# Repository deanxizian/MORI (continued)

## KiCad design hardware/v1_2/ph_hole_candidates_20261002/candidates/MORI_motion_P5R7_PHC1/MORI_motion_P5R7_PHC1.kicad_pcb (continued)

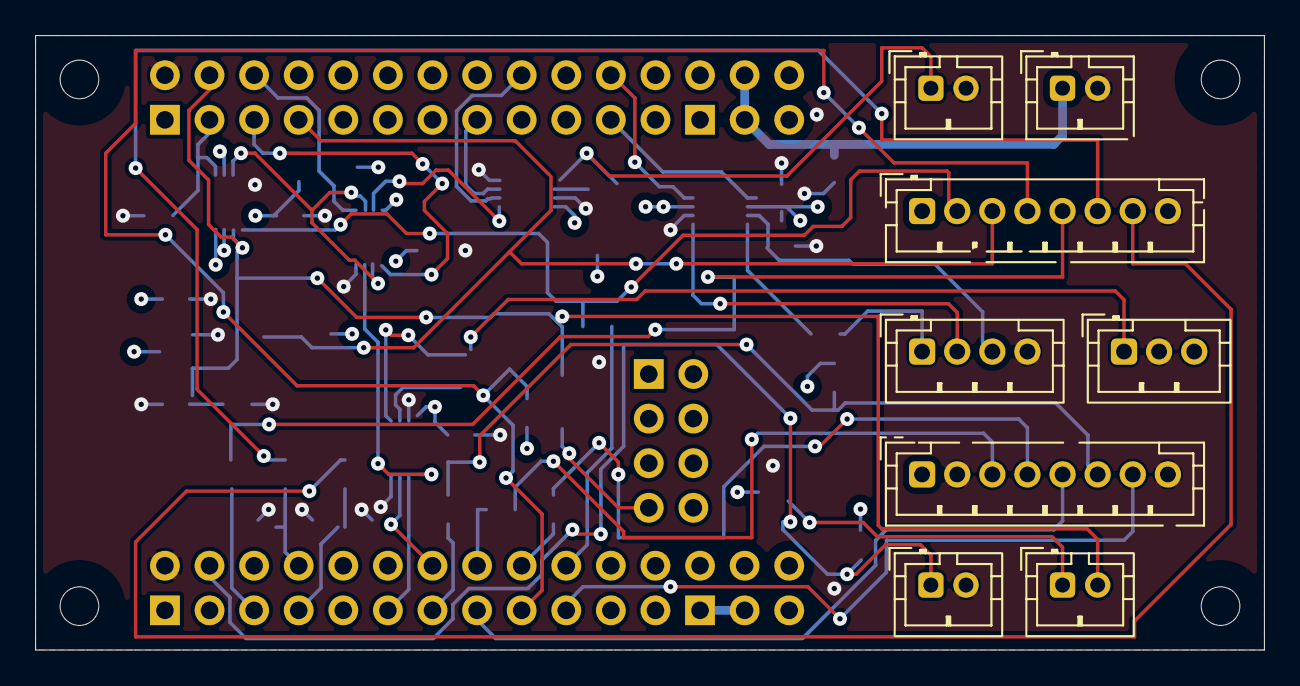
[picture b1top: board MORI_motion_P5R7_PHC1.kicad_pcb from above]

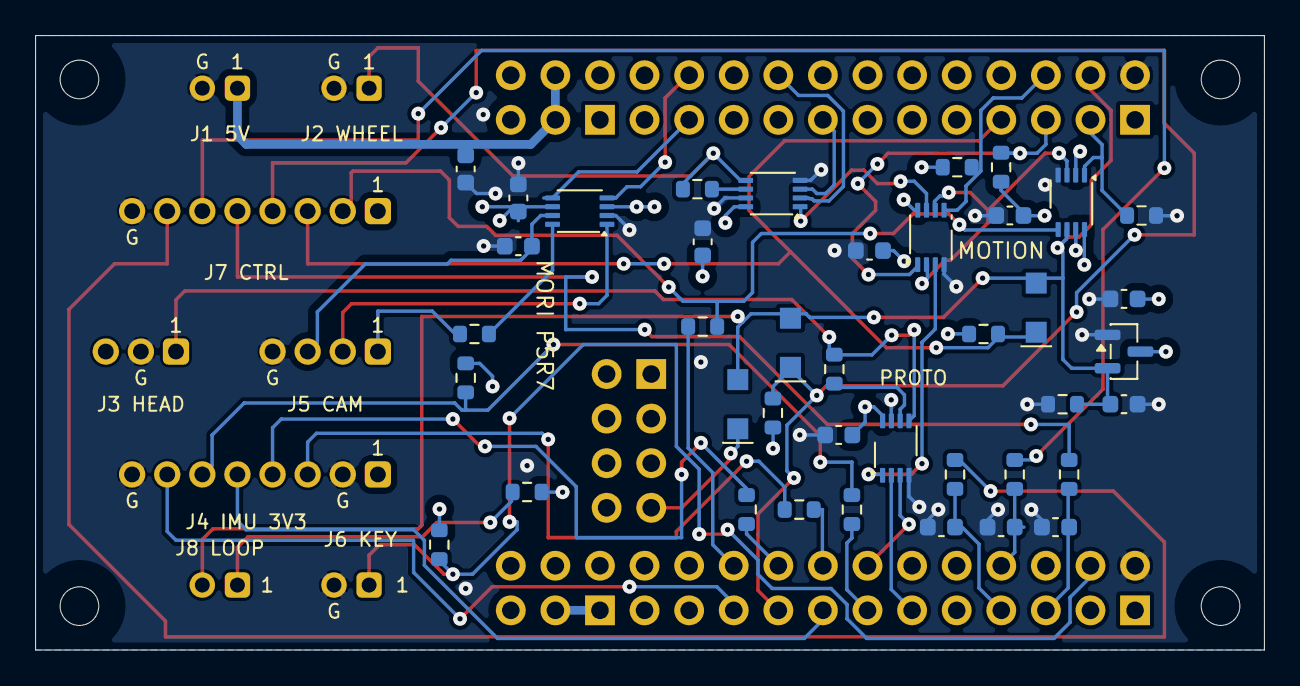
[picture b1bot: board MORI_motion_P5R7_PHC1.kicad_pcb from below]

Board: 4 copper layers, 70.0 x 35.0 mm, 53 parts (40 on the bottom side), 45 nets.

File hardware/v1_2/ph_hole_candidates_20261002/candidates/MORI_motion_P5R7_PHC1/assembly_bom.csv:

ref,value,footprint,source,note
U100,WeAct STM32F412RET6 64Pin V1.1,MORI_Custom:WeAct_F4_64Pin_V11_ECorrected_P5R7,https://github.com/WeActStudio/WeActStudio.STM32F4_64Pin_CoreBoard,"A=P1 B=P2 C=P3 D=P4 E=P5. Component side UP; all male pins DOWN from core underside. E pads shifted native X+2.54mm. Only E7 NRST is connected on carrier; other E pins NC on carrier. E8 is core3V3, not a carrier supply input. Candidate female sockets 61303021821x2 +61300821821; straight E male61300821121. Stack/mating/retention NOT_TESTED; see formal P5R7 handoff. Top SWD test access needs mechanical confirmation after changing from right-angle E header."
J1,MOTION 5V IN,MORI_Custom:JST_PH_B2B-PH-K_1x02_P2.00mm_Vertical__P4_PH_ANNULUS__P5_J1__PHC1_H85_L145,https://www.jst-mfg.com/product/pdf/eng/ePH.pdf,P4 PH 2.0 mm. PHR-2 / SPH-002T-P0.5S. Signal pin numbering unchanged. Check both mating views; never wire by color alone.
J2,S288 DATA ONLY,MORI_Custom:JST_PH_B2B-PH-K_1x02_P2.00mm_Vertical__P4_PH_ANNULUS__PHC1_H85_L145,https://www.jst-mfg.com/product/pdf/eng/ePH.pdf,P4 PH 2.0 mm. PHR-2 / SPH-002T-P0.5S. Signal pin numbering unchanged. Check both mating views; never wire by color alone.
J3,HEAD DATA ONLY,MORI_Custom:JST_PH_B3B-PH-K_1x03_P2.00mm_Vertical__P4_PH_ANNULUS__PHC1_H90_L150,https://www.jst-mfg.com/product/pdf/eng/ePH.pdf,P4 PH 2.0 mm. PHR-3 / SPH-002T-P0.5S. Signal pin numbering unchanged. Check both mating views; never wire by color alone.
J4,BODY IMU SPI,MORI_Custom:JST_PH_B8B-PH-K_1x08_P2.00mm_Vertical__P4_PH_ANNULUS__P5_J4__PHC1_H90_L150,https://www.jst-mfg.com/product/pdf/eng/ePH.pdf,P4 PH 2.0 mm. PHR-8 / SPH-002T-P0.5S. Signal pin numbering unchanged. Check both mating views; never wire by color alone.
J5,CAM J11 MATCH,MORI_Custom:JST_PH_B4B-PH-K_1x04_P2.00mm_Vertical__P4_PH_ANNULUS__PHC1_H90_L150,https://www.jst-mfg.com/product/pdf/eng/ePH.pdf,P4 PH 2.0 mm. PHR-4 / SPH-002T-P0.5S. Signal pin numbering unchanged. Check both mating views; never wire by color alone.
J6,INTERNAL SERVICE KEY,MORI_Custom:JST_PH_B2B-PH-K_1x02_P2.00mm_Vertical__P4_PH_ANNULUS__PHC1_H85_L145,https://www.jst-mfg.com/product/pdf/eng/ePH.pdf,P4 PH 2.0 mm. PHR-2 / SPH-002T-P0.5S. Signal pin numbering unchanged. Check both mating views; never wire by color alone.
J7,POWER CONTROL,MORI_Custom:JST_PH_B8B-PH-K_1x08_P2.00mm_Vertical__P4_PH_ANNULUS__P3R1_J7__PHC1_H90_L150,https://www.jst-mfg.com/product/pdf/eng/ePH.pdf,P4 PH 2.0 mm. PHR-8 / SPH-002T-P0.5S. Signal pin numbering unchanged. Check both mating views; never wire by color alone.
J8,LATCHED ENABLE LOOP,MORI_Custom:JST_PH_B2B-PH-K_1x02_P2.00mm_Vertical__P4_PH_ANNULUS__PHC1_H85_L145,https://www.jst-mfg.com/product/pdf/eng/ePH.pdf,P4 PH 2.0 mm. PHR-2 / SPH-002T-P0.5S. Signal pin numbering unchanged. Check both mating views; never wire by color alone.
U1,SN74LVC2G125DCUR,MORI_Custom:TI_DCU0008A_0p85x0p30,https://www.ti.com/lit/ds/symlink/sn74lvc2g125.pdf,Ioff; bus input 0..5.5V. External actuator VIH/VOH not yet verified. Default no transmission.
U2,SN74LVC2G125DCUR,MORI_Custom:TI_DCU0008A_0p85x0p30__P5_U2,https://www.ti.com/lit/ds/symlink/sn74lvc2g125.pdf,Ioff; bus input 0..5.5V. External actuator VIH/VOH not yet verified. Default no transmission.
U3,SN74LVC2G32DCUR,MORI_Custom:TI_DCU0008A_0p85x0p30__P5_U3,https://www.ti.com/lit/ds/symlink/sn74lvc2g32.pdf,
U4,TXU0202DCUR,MORI_Custom:TI_DCU0008A_0p85x0p30,https://www.ti.com/lit/ds/symlink/txu0202.pdf,"VCC isolation and Ioff; J11.3 powers only translator B rail, never feeds motion regulator."
U5,SN74LVC1G74DCUR,MORI_Custom:TI_DCU0008A_0p85x0p30__P5_U5,https://www.ti.com/lit/ds/symlink/sn74lvc1g74.pdf,Physical loop + supervisor + faults clear latch; only a new explicit ARM rising edge re-enables.
U6,TLV803EA29DBZR,Package_TO_SOT_SMD:SOT-23,https://www.ti.com/lit/ds/symlink/tlv803e.pdf,"2.93V threshold,200ms reset; exact non-R/non-V pinout."
D1,"BAT54H,115",MORI_Custom:BAT54H_SOD123F_Nexperia_20241008_P5R6,,"Cathode pin1; pulls latch clear low, does not reset MCU on ordinary disable."
D2,"BAT54H,115",MORI_Custom:BAT54H_SOD123F_Nexperia_20241008_P5R6,,"Cathode pin1; pulls latch clear low, does not reset MCU on ordinary disable."
D3,"BAT54H,115",MORI_Custom:BAT54H_SOD123F_Nexperia_20241008_P5R6,,"Cathode pin1; pulls latch clear low, does not reset MCU on ordinary disable."
R1,68,Resistor_SMD:R_0603_1608Metric,,
R2,68,Resistor_SMD:R_0603_1608Metric,,
R3,10k,Resistor_SMD:R_0603_1608Metric,,
R4,10k,Resistor_SMD:R_0603_1608Metric,,
R5,10k,Resistor_SMD:R_0603_1608Metric,,
R6,1k,Resistor_SMD:R_0603_1608Metric,,
R7,10k,Resistor_SMD:R_0603_1608Metric,,
R8,10k,Resistor_SMD:R_0603_1608Metric,,
R9,47,Resistor_SMD:R_0603_1608Metric,,
R10,33,Resistor_SMD:R_0603_1608Metric,,
R11,33,MORI_Custom:R_0603_1608Metric__P5_R11,,
R12,33,Resistor_SMD:R_0603_1608Metric,,
R13,10k,Resistor_SMD:R_0603_1608Metric,,
R14,1k,Resistor_SMD:R_0603_1608Metric,,
R15,1k,Resistor_SMD:R_0603_1608Metric,,
R16,1k,Resistor_SMD:R_0603_1608Metric,,
R17,10k,Resistor_SMD:R_0603_1608Metric,,
R18,10k,Resistor_SMD:R_0603_1608Metric,,
R19,1k,Resistor_SMD:R_0603_1608Metric,,
C1,100n,Capacitor_SMD:C_0603_1608Metric,,
C2,100n,Capacitor_SMD:C_0603_1608Metric,,
C3,100n,MORI_Custom:C_0603_1608Metric__P5_C3,,
C4,100n,Capacitor_SMD:C_0603_1608Metric,,
C5,100n,Capacitor_SMD:C_0603_1608Metric,,
C6,100n,Capacitor_SMD:C_0603_1608Metric,,
C7,100n,Capacitor_SMD:C_0603_1608Metric,,
C8,10u,Capacitor_SMD:C_0603_1608Metric,,
C9,10n,Capacitor_SMD:C_0603_1608Metric,,
C10,10n,MORI_Custom:C_0603_1608Metric__P5_C10,,
C11,10n,MORI_Custom:C_0603_1608Metric__P5_C11,,
C12,100n,Capacitor_SMD:C_0603_1608Metric,,
H1,M2 clearance,MountingHole:MountingHole_2.2mm_M2,,
H2,M2 clearance,MountingHole:MountingHole_2.2mm_M2,,
H3,M2 clearance,MountingHole:MountingHole_2.2mm_M2,,
H4,M2 clearance,MountingHole:MountingHole_2.2mm_M2,,

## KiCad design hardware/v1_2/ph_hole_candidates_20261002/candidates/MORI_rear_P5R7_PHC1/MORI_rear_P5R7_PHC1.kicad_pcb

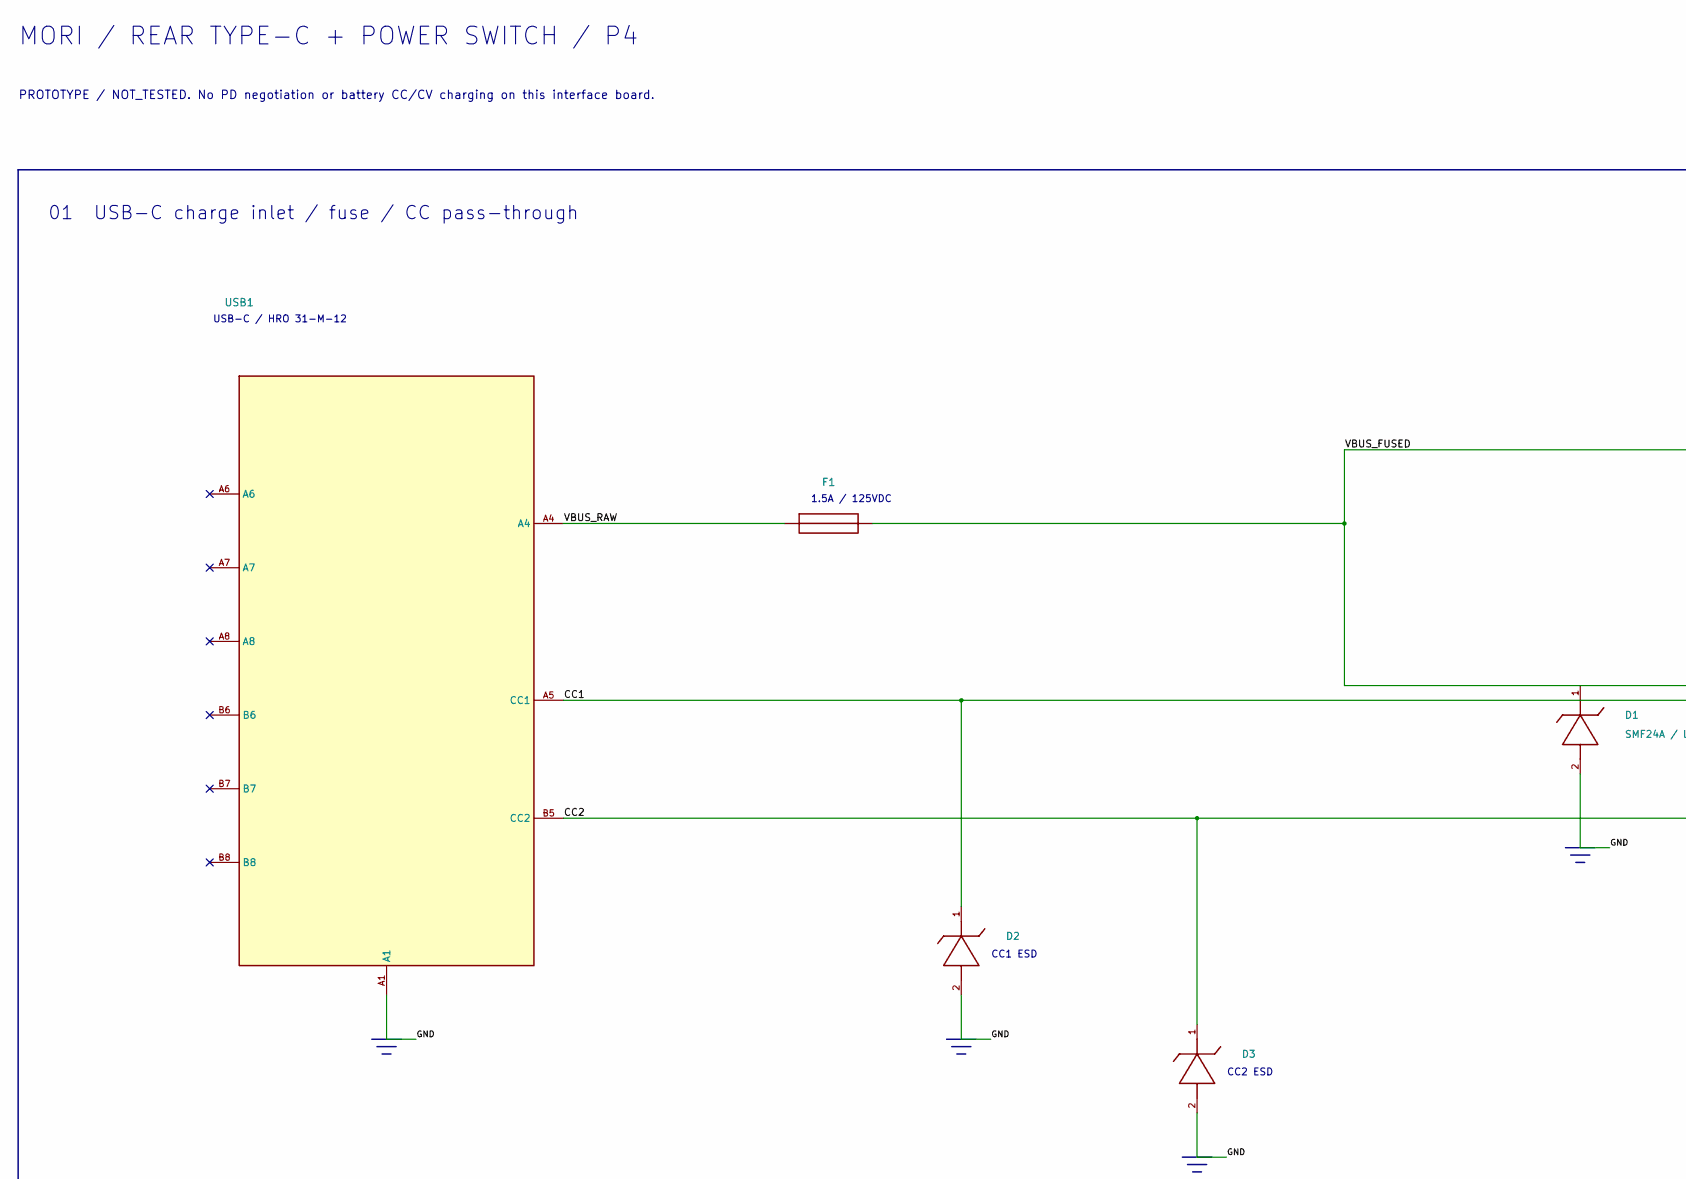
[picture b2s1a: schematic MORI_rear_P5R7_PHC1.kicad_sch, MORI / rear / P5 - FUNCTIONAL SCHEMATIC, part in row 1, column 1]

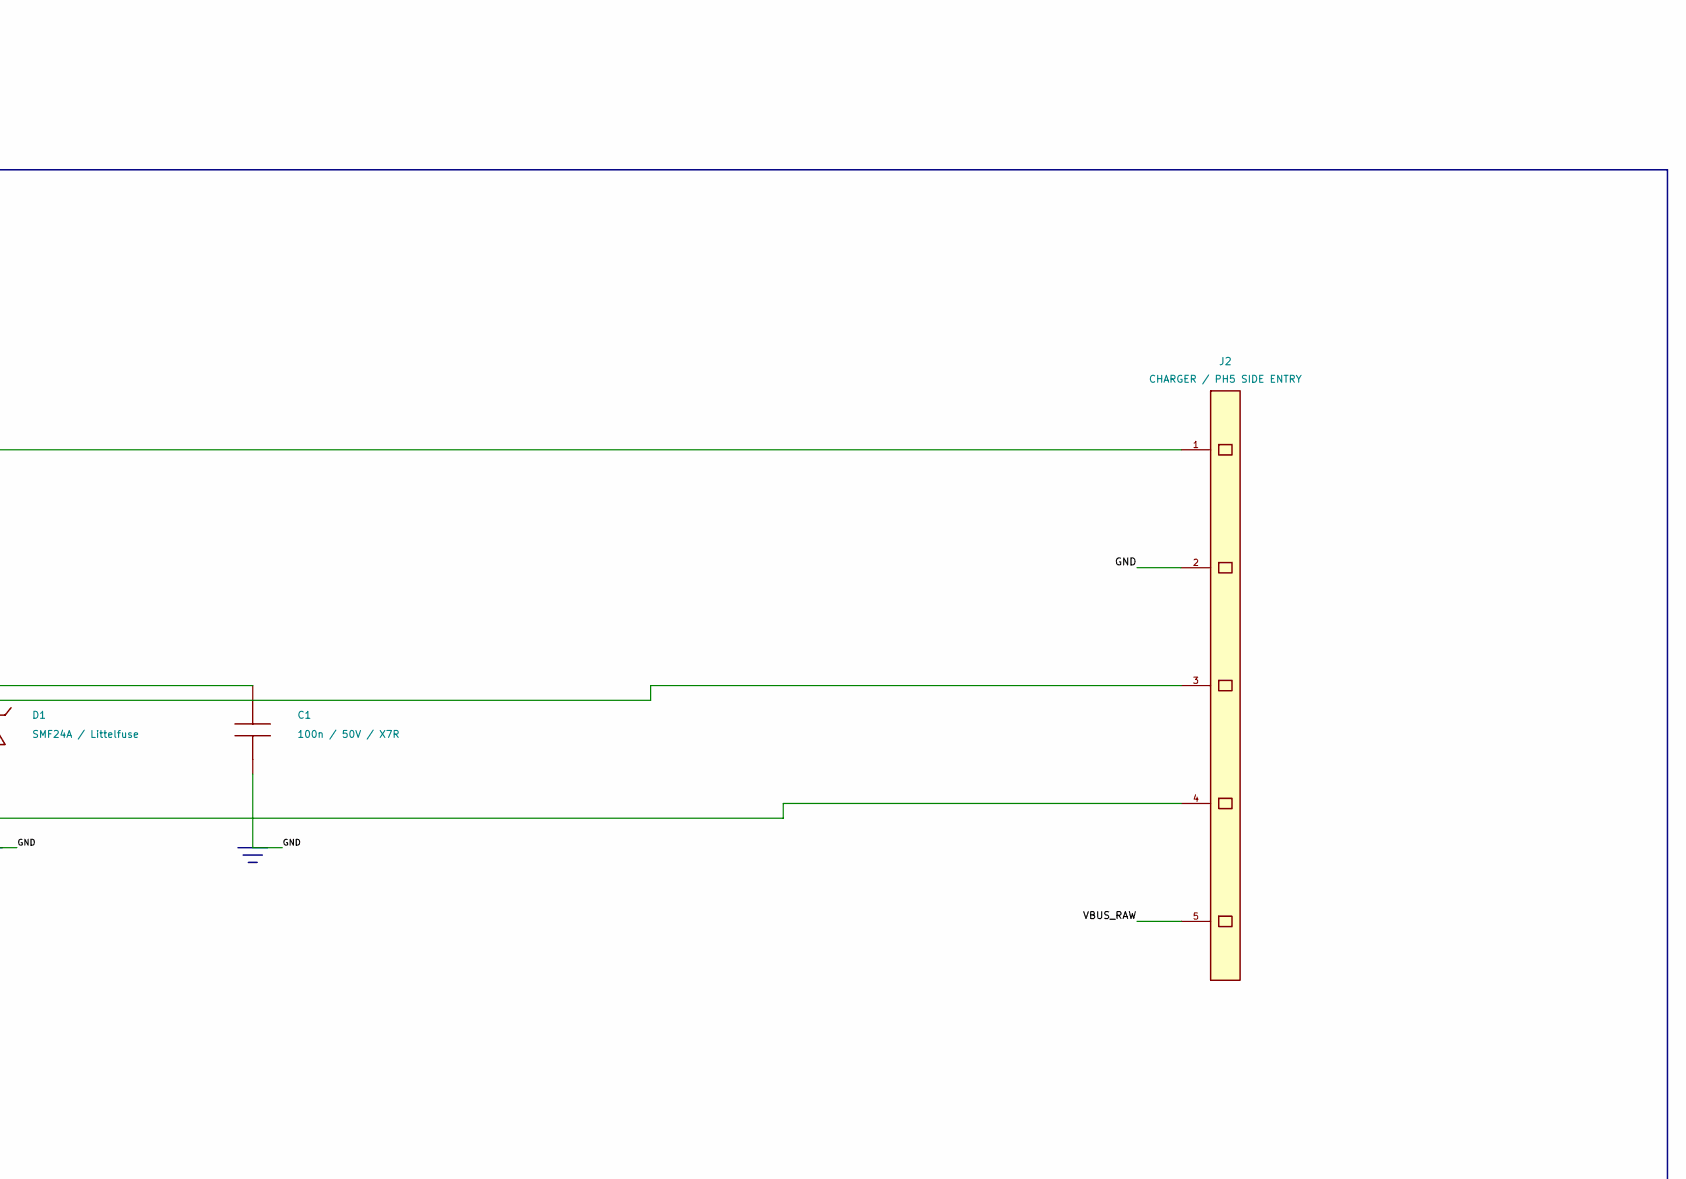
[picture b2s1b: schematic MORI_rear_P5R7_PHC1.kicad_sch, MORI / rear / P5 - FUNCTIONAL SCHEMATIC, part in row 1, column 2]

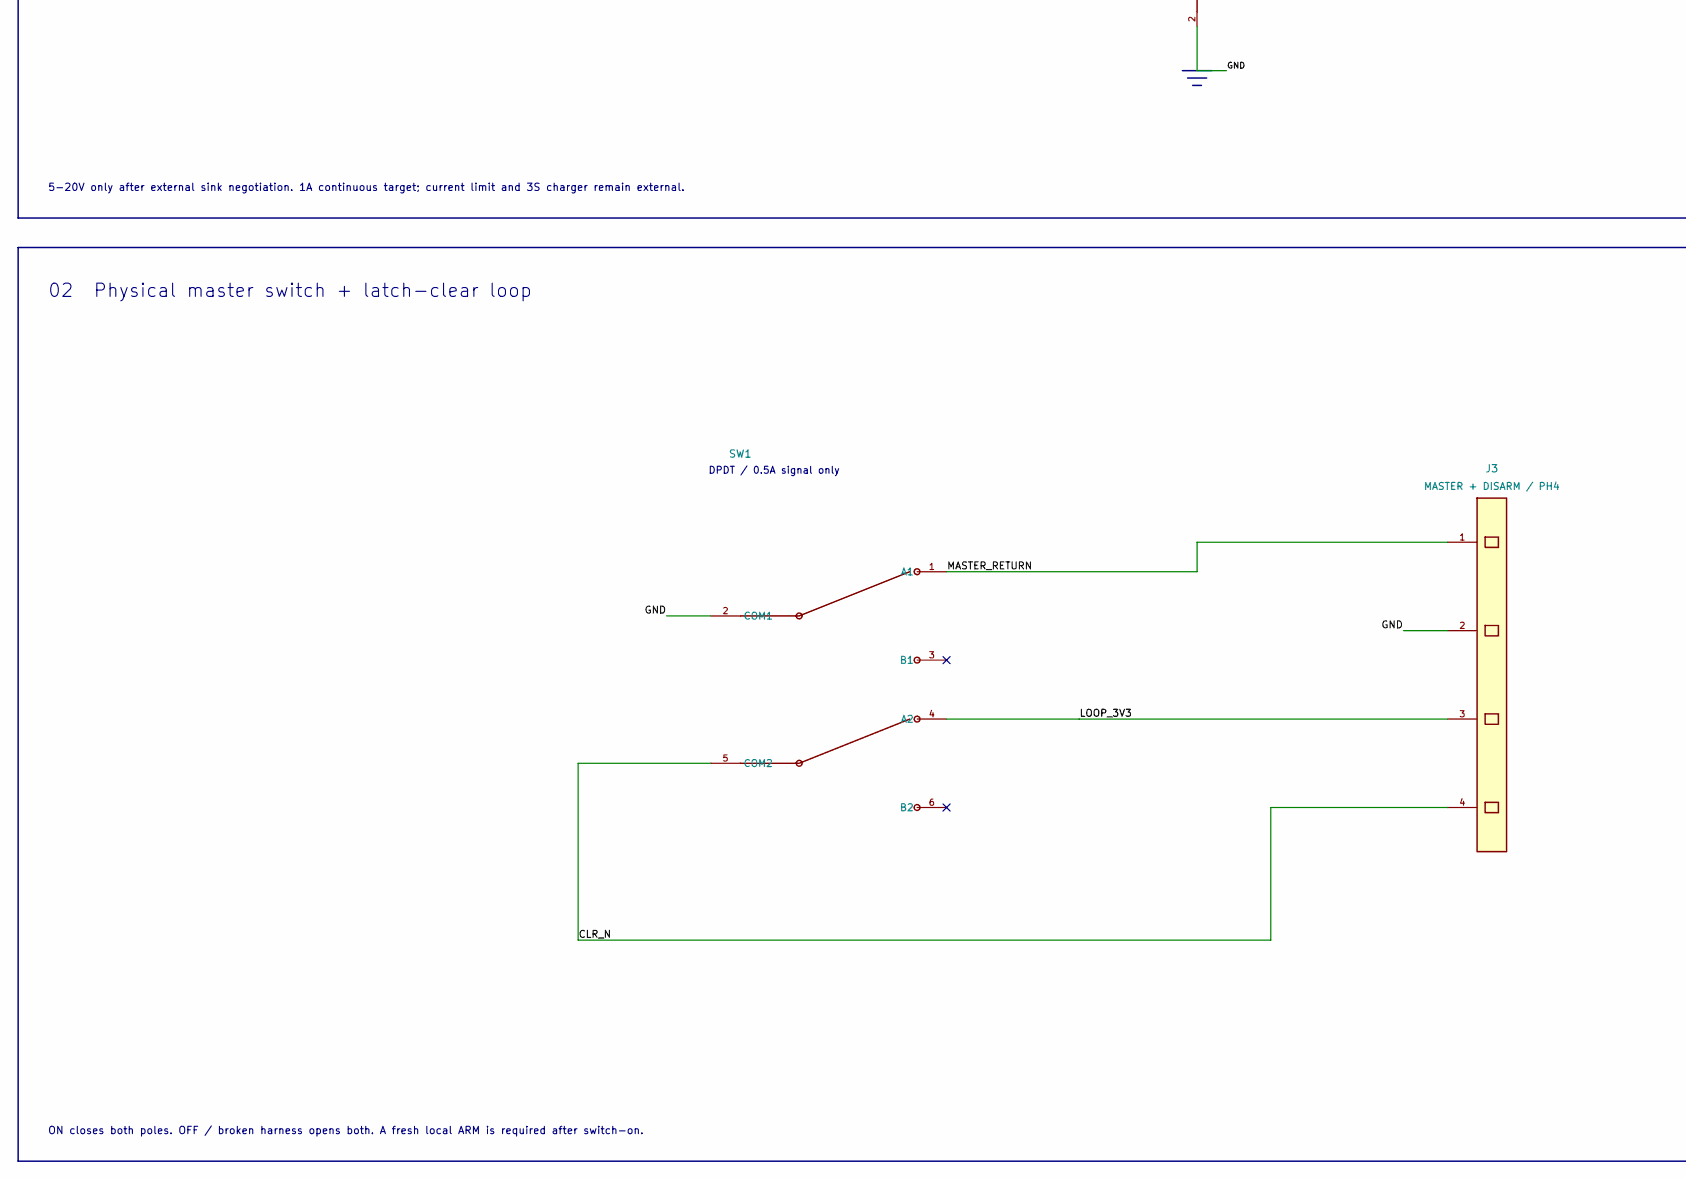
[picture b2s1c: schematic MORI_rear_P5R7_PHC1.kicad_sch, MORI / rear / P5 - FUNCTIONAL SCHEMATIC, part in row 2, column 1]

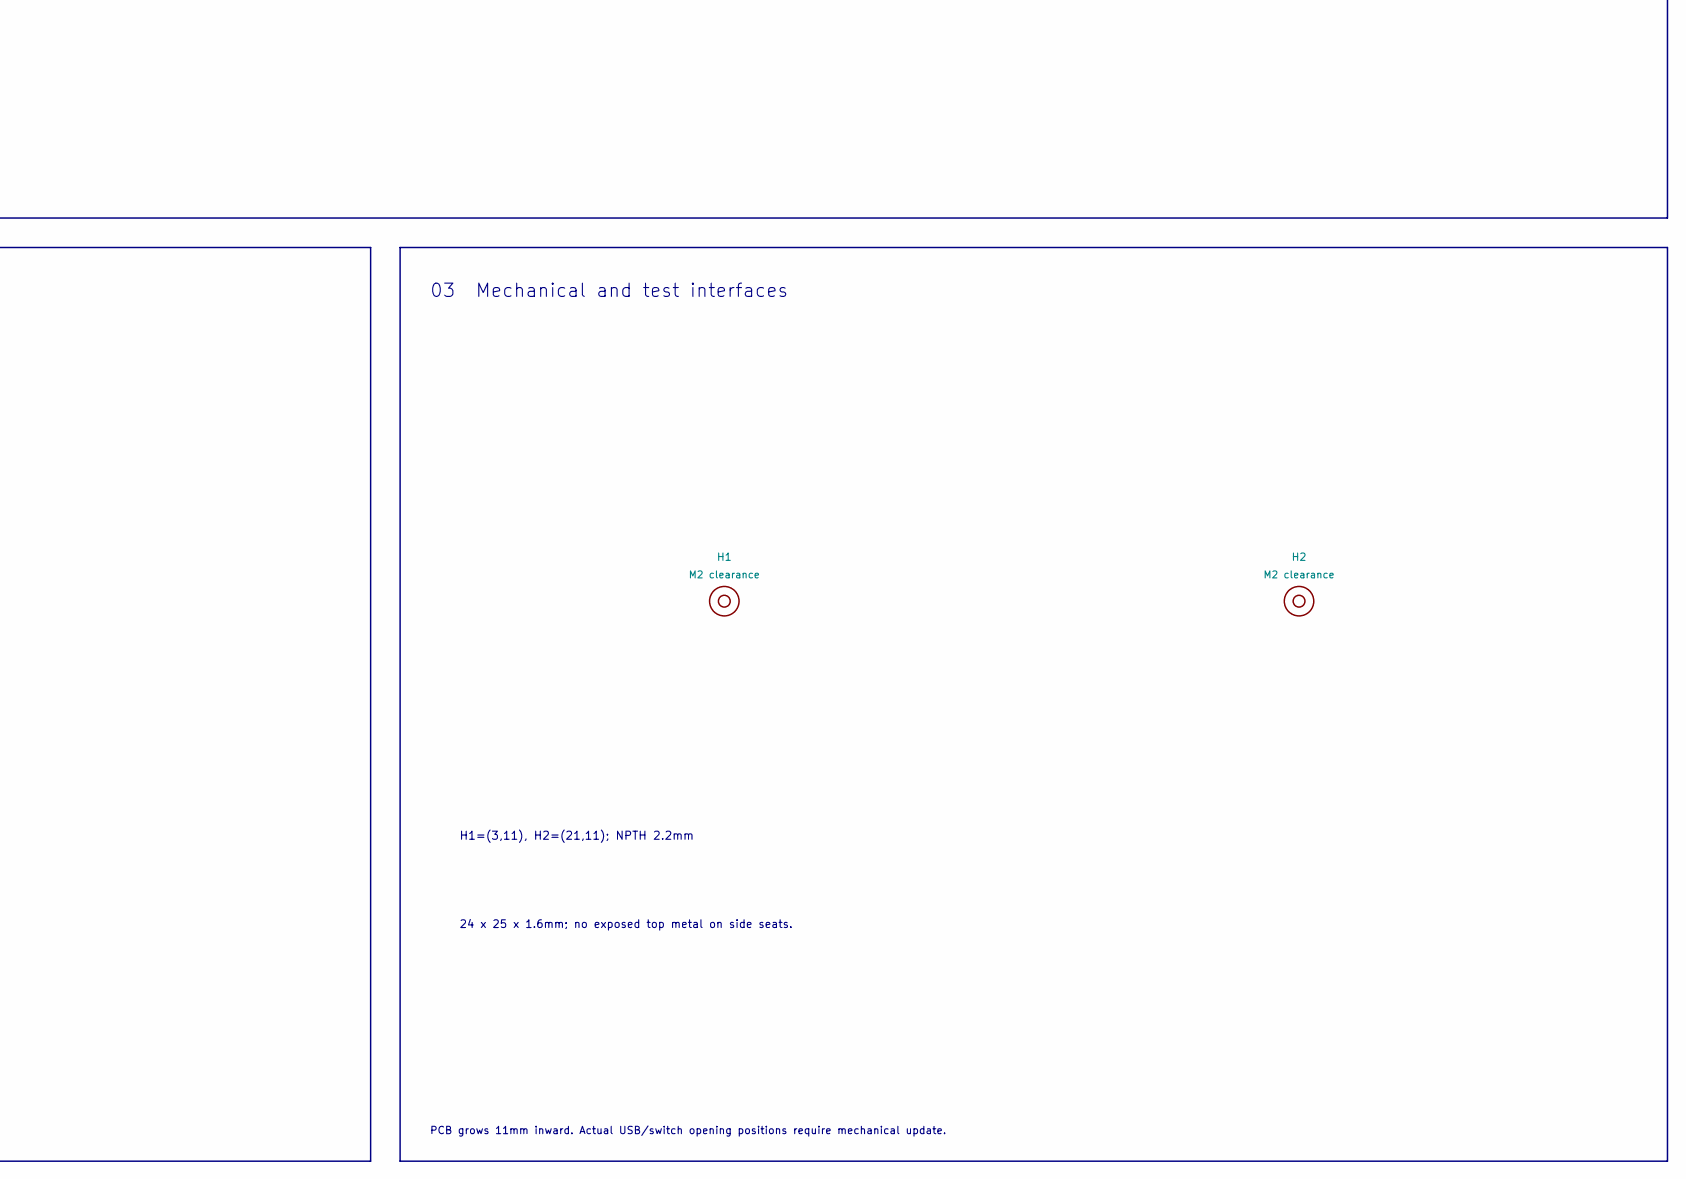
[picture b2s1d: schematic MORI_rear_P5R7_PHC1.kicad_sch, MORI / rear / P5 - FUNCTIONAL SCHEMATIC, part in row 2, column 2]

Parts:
C1: 100n / 50V / X7R; C_0603_1608Metric
D1: SMF24A / Littelfuse; D_SOD-123F__P5_D1
D2: PESD5V0L1BA,115; D_SOD-323__P5_D2
D3: PESD5V0L1BA,115; D_SOD-323__P5_D3
F1: 045101.5MRL / 1.5A; Littelfuse_451_6.1x2.69_P4__P3R1_F1
H1, H2: M2 clearance; MountingHole_2.2mm_M2
J2: CHARGER / PH5 SIDE ENTRY; JST_PH_S5B-PH-K_1x05_P2.00mm_Horizontal__P4_ANNULUS__P5_J2_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
J3: MASTER + DISARM / PH4; JST_PH_B4B-PH-K_1x04_P2.00mm_Vertical__P4_ANNULUS__P3R1_J3_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
SW1: SOFNG MS-202V-G3; SOFNG_MS202V_G3_P4__P5_SW1
USB1: HRO TYPE-C-31-M-12 / charge only; USB_C_Receptacle_HRO_TYPE-C-31-M-12__P4_ANNULUS__P5_USB1

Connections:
/CC1: D2.1, J2.3, USB1.A5 (CC1)
/CC2: D3.1, J2.4, USB1.B5 (CC2)
/CLR_N: J3.4, SW1.5 (COM2)
/GND: C1.2, D1.2, D2.2, D3.2, J2.2, J3.2, SW1.2 (COM1), USB1.A1, USB1.A12, USB1.B1, USB1.B12, USB1.SH
/LOOP_3V3: J3.3, SW1.4 (A2)
/MASTER_RETURN: J3.1, SW1.1 (A1)
/VBUS_FUSED: C1.1, D1.1, F1.2, J2.1
/VBUS_RAW: F1.1, J2.5, USB1.A4, USB1.A9, USB1.B4, USB1.B9

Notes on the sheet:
MORI / REAR TYPE-C + POWER SWITCH / P4
PROTOTYPE / NOT_TESTED. No PD negotiation or battery CC/CV charging on this interface board.
01 USB-C charge inlet / fuse / CC pass-through
5-20V only after external sink negotiation. 1A continuous target; current limit and 3S charger remain external.
USB-C / HRO 31-M-12
1.5A / 125VDC
CC1 ESD
CC2 ESD
02 Physical master switch + latch-clear loop
ON closes both poles. OFF / broken harness opens both. A fresh local ARM is required after switch-on.
DPDT / 0.5A signal only
03 Mechanical and test interfaces
PCB grows 11mm inward. Actual USB/switch opening positions require mechanical update.
H1=(3,11), H2=(21,11); NPTH 2.2mm
24 x 25 x 1.6mm; no exposed top metal on side seats.

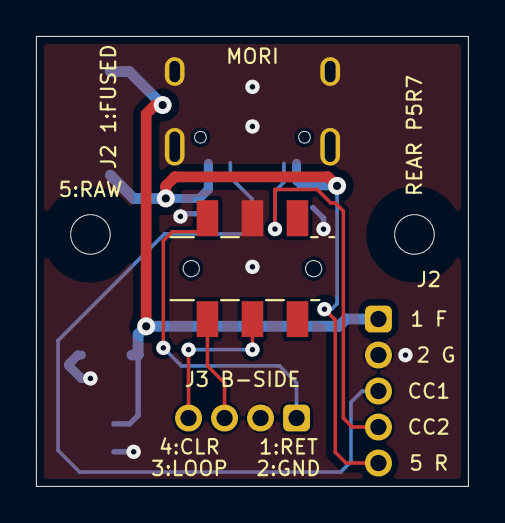
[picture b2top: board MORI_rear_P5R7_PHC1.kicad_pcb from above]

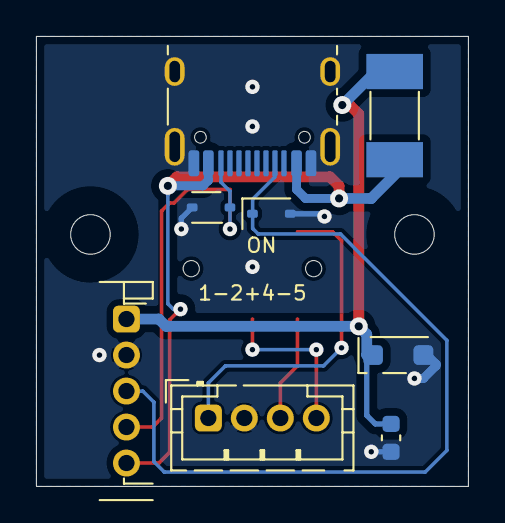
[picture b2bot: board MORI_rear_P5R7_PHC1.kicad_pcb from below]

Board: 2 copper layers, 24.0 x 25.0 mm, 11 parts (8 on the bottom side), 8 nets.

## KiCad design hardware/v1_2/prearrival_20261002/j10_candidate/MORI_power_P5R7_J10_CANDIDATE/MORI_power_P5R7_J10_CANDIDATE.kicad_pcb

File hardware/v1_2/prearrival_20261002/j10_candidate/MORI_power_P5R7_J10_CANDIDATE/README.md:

# J10 侧出线试装候选 C1

PROTOTYPE / NOT FOR FABRICATION. 保持 P5R6 孔位、针序和铜线，仅变更 J10 封装及其本体规则区。原版不变。

此目录用于暴露固定孔位替换的碰撞，不能因有原生文件就称为通过。真实 DRC/ERC 与几何结果在 ../reports/。未导出生产文件，完整机械插拔与线束仍待复核。

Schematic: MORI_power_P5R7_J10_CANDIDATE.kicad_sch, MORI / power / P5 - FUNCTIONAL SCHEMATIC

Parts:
C1, C20: 100n; C_0603_1608Metric
C2: 1u 25V; C_0603_1608Metric__P3_C2
C10: Panasonic EEU-FR1C102 1000uF 16V; CP_Radial_D10.0mm_P5.00mm__P2_C10__P3_C10__P5_C10
C21, C41: 10n; C_0603_1608Metric
C30: Panasonic EEU-FR1C102 1000uF 16V; CP_Radial_D10.0mm_P5.00mm__P3_C30__P5_C30
C40: 100n; C_0603_1608Metric__P5_C40
C60: 22u / 25V / X7R; C_1210_3225Metric__P3_C60__P3R1_C60
C61: 100n / 50V / X7R; C_0603_1608Metric__P5_C61
C62, C72: 100n / 50V / X7R; C_0603_1608Metric
C63: 22u / 25V / X7R; C_1210_3225Metric__P5_C63
C64, C66, C73, C76: 22u / 25V / X7R; C_1210_3225Metric
C65: 75p / 50V / C0G; C_0603_1608Metric__P5_C65
C70: 22u / 25V / X7R; C_1210_3225Metric__P3_C70
C71: 100n / 50V / X7R; C_0603_1608Metric__P5_C71
C74: 22u / 25V / X7R; C_1210_3225Metric__P3_C74
C75: 75p / 50V / C0G; C_0603_1608Metric__P3R1_C75
D1, D20, D90: BZT52H-C10,115; D_SOD-123F
D10: B540C-13-F; D_SMC__P3_D10__P5_D10
D30: B540C-13-F; D_SMC__P5_D30
D40: BZT52H-C10,115; D_SOD-123F__P5_D40
F60: 1A / 125V / very fast; Fuse_Littelfuse-NANO2-451_453
F70: 2A / 125V / very fast; Fuse_Littelfuse-NANO2-451_453__P5_F70
H1, H2, H3, H4: M2 mounting / POSITION TBD; MountingHole_2.2mm_M2
J1: PACK AFTER 6.3A FUSE; AMASS_XT30UPB-M_1x02_P5.0mm_Vertical__P3_J1
J2: WHEEL BUCK VIN; AMASS_XT30UPB-M_1x02_P5.0mm_Vertical__P3_J2__P5_J2
J3: WHEEL BUCK 9V RETURN; AMASS_XT30UPB-M_1x02_P5.0mm_Vertical__P3R1_J3
J4: HEAD BUCK VIN; AMASS_XT30UPB-M_1x02_P5.0mm_Vertical__P2_J4__P3_J4__P3R1_J4
J5: HEAD BUCK 6V RETURN; AMASS_XT30UPB-M_1x02_P5.0mm_Vertical__P2_J5__P3_J5__P5_J5
J6: BAT_MON SERVICE / DNP; AMASS_XT30UPB-M_1x02_P5.0mm_Vertical__P3_J6__P3R1_J6; not fitted
J7: S288 L; JST_XH_B3B-XH-A_1x03_P2.50mm_Vertical__P2_J7__P3_J7__P5_J7
J8: S288 R; JST_XH_B3B-XH-A_1x03_P2.50mm_Vertical__P2_J8__P5_J8
J9: SCS0009 CHAIN; JST_XH_B3B-XH-A_1x03_P2.50mm_Vertical__P5_J9
J10: MOTION CONTROL; JST_PH_S8B-PH-K_1x08_P2.00mm_Horizontal__MORI_1p35land_0p75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
J11: WHEEL DUMP 5R6 EXTERNAL; AMASS_XT30UPB-M_1x02_P5.0mm_Vertical__P5R5_DUMP
J12: HEAD DUMP 10R EXTERNAL; AMASS_XT30UPB-M_1x02_P5.0mm_Vertical__P2_J12__P5_J12__P5R5_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
J13: S288 DATA; JST_PH_B2B-PH-K_1x02_P2.00mm_Vertical__P4_PH_ANNULUS
J14: HEAD DATA; JST_PH_B3B-PH-K_1x03_P2.00mm_Vertical__P4_PH_ANNULUS
J15: CHARGE INTERLOCK; JST_PH_B2B-PH-K_1x02_P2.00mm_Vertical__P4_PH_ANNULUS__P3R1_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
J16: CHARGER RAW VBUS SENSE; JST_PH_B2B-PH-K_1x02_P2.00mm_Vertical__P4_PH_ANNULUS__P3R1_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
J17: MOTION 5V OUT / 1+ 2GND; JST_PH_B2B-PH-K_1x02_P2.00mm_Vertical__P4_PH_ANNULUS
J18: CAM 5V OUT / 1+ 2GND; JST_XH_B2B-XH-A_1x02_P2.50mm_Vertical
J19: REAR MASTER / 1RETURN 2GND; JST_PH_B2B-PH-K_1x02_P2.00mm_Vertical__P4_PH_ANNULUS__P5_J19
JP60: SERVICE OFF / OPEN=ON; PinHeader_1x02_P2.54mm_Vertical__P3_JP60__P3R1_JP60
JP70: SERVICE OFF / OPEN=ON; PinHeader_1x02_P2.54mm_Vertical__P5_JP70
L60, L70: 10uH / SRP7050TA-100M; Bourns_SRP7050TA_8p4_span_2p5_gap
Q1: AO4407A; SOIC-8_3.9x4.9mm_P1.27mm__P5_Q1
Q10, Q90: AO4407A; SOIC-8_3.9x4.9mm_P1.27mm
Q11: AO3400A; SOT-23__P5_Q11
Q20, Q31, Q40: AO3400A; SOT-23
Q30: AO4407A; SOIC-8_3.9x4.9mm_P1.27mm__P5_Q30
Q50: MMBT3904LT1G; SOT-23__P5_Q50
R1, R30, R91: 10k; R_0603_1608Metric
R2: WSL2512R0100FEA 10mR 1% 1W; R_2512_6332Metric
R3, R4: 0; R_0603_1608Metric
R10: 10k; R_0603_1608Metric__P5_R10
R11: 100; R_0603_1608Metric__P5_R11
R20, R24, R40, R44: 2.2k; R_0603_1608Metric
R21: 33.2k 0.1%; R_0603_1608Metric
R22: 10k 0.1%; R_0603_1608Metric__P5_R22
R23, R43: 1M 0.1%; R_0603_1608Metric
R25: 37.4k 0.1%; R_0603_1608Metric
R26, R42, R46: 10k 0.1%; R_0603_1608Metric
R31: 100; R_0603_1608Metric__P5_R31
R41: 16.5k 0.1%; R_0603_1608Metric
R45: 18.7k 0.1%; R_0603_1608Metric__P5_R45
R50, R52: 100k 0.1%; R_0603_1608Metric
R51, R53: 27k 0.1%; R_0603_1608Metric
R54: 10k; R_0603_1608Metric__P5_R54
R55: 47k; R_0603_1608Metric
R56: 100k; R_0603_1608Metric__P5_R56
R60, R70: 100k / 0.1%; R_0603_1608Metric
R61: 13.3k / 0.1%; R_0603_1608Metric
R71: 13.3k / 0.1%; R_0603_1608Metric__P3_R71
R90: 100k; R_0603_1608Metric
TP60: +5V_MOTION; TestPoint_Pad_D1.5mm__P3_TP60
TP61: GND; TestPoint_Pad_D1.5mm__P5_TP61
TP70: +5V_CAM; TestPoint_Pad_D1.5mm__P3R1_TP70
TP71: GND; TestPoint_Pad_D1.5mm__P5_TP71
U1: INA180A1IDBVR; SOT-23-5__P5_U1
U20: LM393BDR; SOIC-8_3.9x4.9mm_P1.27mm__P5_U20
U21: TL431BIDBZR; SOT-23
U40: LM393BDR; SOIC-8_3.9x4.9mm_P1.27mm__P5_U40
U41: TL431BIDBZR; SOT-23__P5_U41
U60, U70: TPS54302DDCR; TI_DDC0006A_TPS54302

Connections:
/+3V3: C1.1, J10.1, U1.5 (VS)
/+5V_CAM: C73.1, C74.1, C75.1, J18.1 (5V_OUT), L70.2, R70.1, TP70.1
/+5V_MOTION: C63.1, C64.1, C65.1, J17.1 (5V_OUT), L60.2, R60.1, TP60.1
/ARM_Q: J10.2, Q11.1, Q31.1, R54.1
/BAT_ADC: J10.5, R50.2, R51.1
/BAT_IN: Q1.5, Q1.6, Q1.7, Q1.8, Q90.5, Q90.6, Q90.7, Q90.8
/BAT_MON: C2.1, F60.1, F70.1, J2.2 (PLUS), J4.2 (PLUS), J6.2 (PLUS), R2.2, R4.1, R50.1
/BAT_REV: D1.1, Q1.1 (SOURCE PROTECTED OUTPUT), Q1.2, Q1.3, R2.1, R3.1
/C5_BOOT: C72.1, U70.6 (BOOT)
/C5_EN: JP70.1 (EN), U70.5 (EN)
/C5_FB: C75.2, R70.2, R71.1, U70.4 (FB)
/C5_SW: C72.2, L70.1, U70.2 (SW)
/C5_VIN: C70.1, C71.1, C76.1, F70.2, U70.3 (VIN)
/CHG_BASE: Q50.1 (B), R55.2, R56.1
/CHG_N: J10.4, J15.1, Q50.3 (C)
/CURRENT_ADC: J10.7, U1.1 (OUT)
/FAULT_N: J10.3, U20.7 (OUT2), U40.7 (OUT2)
/GND: C1.2, C2.2, C10.2, C20.2, C21.2, C30.2, C40.2, C41.2, C60.2, C61.2, C63.2, C64.2, C66.2, C70.2, C71.2, C73.2, C74.2, C76.2, D20.2, D40.2, J1.1 (MINUS), J2.1 (MINUS), J3.1 (MINUS), J4.1 (MINUS), J5.1 (MINUS), J6.1 (MINUS), J7.1 (GND), J8.1 (GND), J9.1 (GND), J10.8, J13.2, J14.2, J15.2, J16.2, J17.2 (GND), J18.2 (GND), J19.2, JP60.2 (GND), JP70.2 (GND), Q11.2, Q20.2, Q31.2, Q40.2, Q50.2 (E), R1.2, R22.2, R26.2, R42.2, R46.2, R51.2, R53.2, R54.2, R56.2, R61.2, R71.2, TP61.1, TP71.1, U1.2 (GND), U20.4 (GND), U21.3 (A), U40.4 (GND), U41.3 (A), U60.1 (GND), U70.1 (GND)
/H6_IN: D30.2, J5.2 (PLUS)
/H_BRAKE_GATE: D40.1, Q40.1, R43.1, R44.2, U40.1 (OUT1)
/H_BUS: J9.3 (BUS), J14.1
/H_DUMP_D: J12.1 (MINUS), Q40.3
/H_GATE: Q30.4, R30.1, R31.1
/H_GATE_LOW: Q31.3, R31.2
/H_OVSENSE: C41.1, R45.2, R46.1, U40.6 (IN2-)
/H_PRE: D30.1, Q30.1, Q30.2, Q30.3, R30.2
/H_REF: R40.2, U40.2 (IN1-), U40.5 (IN2+), U41.1 (K), U41.2 (REF)
/H_SENSE: R41.2, R42.1, R43.2, U40.3 (IN1+)
/H_VM: C30.1, C40.1, J9.2 (V+), J12.2 (PLUS), Q30.5 (DRAIN SWITCHED OUTPUT), Q30.6, Q30.7, Q30.8, R40.1, R41.1, R44.1, R45.1, U40.8 (VCC)
/KELVIN_N: R4.2, U1.4 (IN-)
/KELVIN_P: R3.2, U1.3 (IN+)
/M5_BOOT: C62.1, U60.6 (BOOT)
/M5_EN: JP60.1 (EN), U60.5 (EN)
/M5_FB: C65.2, R60.2, R61.1, U60.4 (FB)
/M5_SW: C62.2, L60.1, U60.2 (SW)
/M5_VIN: C60.1, C61.1, C66.1, F60.2, U60.3 (VIN)
/MASTER_GATE: D90.2, Q90.4, R90.2, R91.1
/MASTER_RETURN: J19.1, R91.2
/PACK_FUSED: D90.1, J1.2 (PLUS), Q90.1, Q90.2, Q90.3, R90.1
/REV_GATE: D1.2, Q1.4, R1.1
/VBUS_CHARGE: J16.1, R55.1
/W9_IN: D10.2, J3.2 (PLUS)
/WHEEL_ADC: J10.6, R52.2, R53.1
/W_BRAKE_GATE: D20.1, Q20.1, R23.1, R24.2, U20.1 (OUT1)
/W_BUS: J7.3 (BUS), J8.3 (BUS), J13.1
/W_DUMP_D: J11.1 (MINUS), Q20.3
/W_GATE: Q10.4, R10.1, R11.1
/W_GATE_LOW: Q11.3, R11.2
/W_OVSENSE: C21.1, R25.2, R26.1, U20.6 (IN2-)
/W_PRE: D10.1, Q10.1, Q10.2, Q10.3, R10.2
/W_REF: R20.2, U20.2 (IN1-), U20.5 (IN2+), U21.1 (K), U21.2 (REF)
/W_SENSE: R21.2, R22.1, R23.2, U20.3 (IN1+)
/W_VM: C10.1, C20.1, J7.2 (V+), J8.2 (V+), J11.2 (PLUS), Q10.5 (DRAIN SWITCHED OUTPUT), Q10.6, Q10.7, Q10.8, R20.1, R21.1, R24.1, R25.1, R52.1, U20.8 (VCC)

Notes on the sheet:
MORI / POWER CONDITIONER / P4
Power flows left to right. Supplies above, returns below. PROTOTYPE / UNVALIDATED.
01 Pack input / reverse protection / shunt
Q90 master stage precedes BAT_IN. No charger on this PCB.
10mR / 1% / 1W
02 Kelvin current sense
Sense from the shunt pads. Discharge-only nominal transfer: 0.2 V/A.
03 Wheel 9 V conditioning
External buck return. Inrush, brake energy and thermal performance: NOT_TESTED.
1000u / 16V
04 Head 6 V conditioning
05 External converter input distribution
J2: wheel buck. J4: head buck. J6: BAT_MON SERVICE / DNP.
06 Wheel rail / brake and overvoltage
Two comparators share one LM393B. External dump resistor needs pulse qualification.
LM393B / brake + fault
5R6 / 5W external
07 Head rail / brake and overvoltage
10R / 5W external
08 Voltage monitor / motion connector
Divider ratio 27 / 127. Current_ADC comes from block 02.
09 Charge insertion / VBUS sense
Sense and interlock only; no CC / PD / CC-CV charger implementation.
10 Supply boundaries / board mounting
80 x 55 mm PCB; populated assembly and thermal performance are not qualified.
Supply boundary
11 Motion 5 V / independent fused buck
Prototype: verify stability, temperature, cable drop and concurrent load. No PCB placement frozen.
1A input fuse
22u/25V
100n
100n BOOT
10uH / 4A rms
MOTION 5V
100k 0.1%
13.3k 0.1%
75p C0G
OPEN=ON / SHORT=OFF
5V probe
GND probe
